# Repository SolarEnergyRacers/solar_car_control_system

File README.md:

`` SolarEnergyRacers

---

# Solar Car Control System

## ESP32 Pinout & Wiring

**_Wiring_**:

## Wiring / Port Usage

| Device:Port         | Functionality          |
| :------------------ | :--------------------- |
| **_ESP32_** | main micro processor   |
| ESP32:22            | I2C:SCL                |
| ESP32:23            | I2C:SDA                |
| ESP32:15            | SERIAL:TX              |
| ESP32:16            | SERIAL:RX              |
| ESP32:18            | SPI:MOSI               |
| ESP32:19            | SPI:MISO               |
| ESP32:5             | SPI:CLK                |
| ESP32:12            | 1Wire                  |
| ESP32:13            | GPIO:LED_BUILTIN       |
| ESP32:33            | GPIO:PCF8574_INTERRUPT |
| ESP32:14            | SPI:CS_SD_CARD         |
| ESP32:32            | SPI:CS_TFT_SCREEN      |
| ESP32:4             | SPI:DC                 |
| ESP32:21            | SPI:RST                |
| ESP32:25 DAC        | CAN:TX                 |
| ESP32:26 DAC        | CAN:RX                 |

| **_ADS1115_** |    Analog to digital converter    |
| :-------------------- | :--------------------------------: |
| ADC0, I2C Addr 0x48   |                                    |
| ADC0:0                | motor controller, speed indication |
| ADC0:1                |    Ibat: battery current sensor    |
| ADC0:2                |     Imot: motor current sensor     |
| ADC0:3                |       Ipv: pv current sensor       |
| ADC1, I2C Addr 0x49   |                                    |
| ADC1:0                |   Ubat: battery voltage (analog)   |
| ADC1:1                |   Umot: motorcontroller voltage   |
| ADC1:2                |                                    |
| ADC1:3                |                                    |
| ADC2, I2C Addr 0x4a   |                                    |
| ADC2:0                | steering wheel acceleration piezo |
| ADC2:1                | steering wheel deceleration piezo |
| ADC2:2                |                                    |
| ADC2:3                |                                    |

| **_MCP23014_** |      Input/Output extender      |
| :--------------------- | :-----------------------------: |
| **IOExt0**       |                                |
| IOExt0:0 in            | switch (status): battery on/off |
| IOExt0:1 in            |   switch (status): PV on/off   |
| IOExt0:2 in            |  switch (status): motor on/off  |
| IOExt0:3               |       ~~mc: eco/power~~       |
| IOExt0:4               |         ~~mc: on/off~~         |
| IOExt0:5 in            |    switch (status): fwd/rwd    |
| IOExt0:6               |         ~~pv: on/off~~         |
| IOExt0:7               |   output: battery fan on/off   |
|                        |                                |
| IOExt1:0               |     output: left indicator     |
| IOExt1:1               |     output: right indicator     |
| IOExt1:2               |          output: horn          |
| IOExt1:3               |       output: head light       |
| IOExt1:4               |          output: light          |
| IOExt1:5               |                                |
| IOExt1:6               |                                |
| IOExt1:7               |                                |
| **IOExt2**       |     steering wheel buttons     |
| IOExt2:0               |     button: left indicator     |
| IOExt2:1               |     button: right indicator     |
| IOExt2:2               |       button: head light       |
| IOExt2:3               |          button: light          |
| IOExt2:4               |          button: horn          |
| IOExt2:5               |          button: next          |
| IOExt2:6               |       button: power/speed       |
| IOExt2:7               |        button: set/reset        |

| **_ILI9341_** |             3.2" 320x240 display             |
| :-------------------- | :------------------------------------------: |
| ILI9341: CS           |         see ESP32:SPI:CS_TFT_SCREEN         |
| ILI9341: MOSI         |              see ESP32:SPI:MOSI              |
| ILI9341: MISO         | see ESP32:SPI:MISO (Pull Down: 10kΏ to GND) |
| ILI9341: CLK          |              see ESP32:SPI:CLK              |
| ILI9341: D/S          |           Pull Down: 10kΏ to GND           |
| ILI9341: SD_CS        |                                              |

| **_DS1803_** |       digital potentiometer       |
| :------------------- | :-------------------------------: |
| SCL:8                |         see ESP32:I2C:SCL         |
| SDA:9                |         see ESP32:I2C:SDA         |
| H0:12                |       VCC at 5V Powersupply       |
| W0:10                |       MC:acceleration input       |
| L0:11                | GND at 5V Powersupply + ESP32:GND |
| H1:1                 |       VCC at 5V Powersupply       |
| W1:3                 |      MC: deceleration input      |
| L1:2                 | GND at 5V Powersupply + ESP32:GND |
| A0:6                 |       GND for address 0x28       |
| A1:5                 |       GND for address 0x28       |
| A0:4                 |       GND for address 0x28       |

| **_DS1307_** | RTC, real time clock |
| :------------------- | :------------------: |
| SCL                  |  see ESP32:I2C:SCL  |
| SDA                  |  see ESP32:I2C:SDA  |

| **_Gyro+Acc_** | gyroscope & accelerator |
| :--------------------- | :---------------------: |
| SCL                    |    see ESP32:I2C:SCL    |
| SDA                    |    see ESP32:I2C:SDA    |

| **_Temp_** | temperature sensor |
| :----------------- | :----------------: |
| Temp0              |  see ESP32:1Wire  |
| Temp1              |  see ESP32:1Wire  |
| Temp2              |  see ESP32:1Wire  |
| Temp3              |  see ESP32:1Wire  |

| **_SD_** |         sd card         |
| :--------------- | :----------------------: |
| CS               | see ESP32:SPI:CS_SD_CARD |
| MOSI             |      see ESP32:MOSI      |
| MISO             |      see ESP32:MISO      |
| CLK              |      see ESP32:CLK      |
| D/S              |        required?        |

| **_Serial_** | serial telemetry communication |
| :------------------- | :----------------------------: |
| RX                   |      see ESP32:SERIAL:RX      |
| TX                   |      see ESP32:SERIAL:TX      |

| **_MPPT_** | maximum power point tracking communication |
| :----------------- | :----------------------------------------: |
| CAN Lo             |              see ESP32:CAN:Lo              |
| CAN Hi             |              see ESP32:CAN:Hi              |

| **_BMS_** | battery management system communication |
| :---------------- | :-------------------------------------: |
| CAN Lo            |            see ESP32:CAN:Lo            |
| CAN Hi            |            see ESP32:CAN:Hi            |

| **_ILI9341_** |             3.2" 320x240 display             |
| :-------------------- | :------------------------------------------: |
| CS                    |         see ESP32:SPI:CS_TFT_SCREEN         |
| MOSI                  |              see ESP32:SPI:MOSI              |
| MISO                  | see ESP32:SPI:MISO (Pull Down: 10kΏ to GND) |
| CLK                   |              see ESP32:SPI:CLK              |
| D/S                   |           Pull Down: 10kΏ to GND           |

| **_DS1803_** |       digital potentiometer       |
| :------------------- | :-------------------------------: |
| SCL:8                |         see ESP32:I2C:SCL         |
| SDA:9                |         see ESP32:I2C:SDA         |
| H0:12                |       VCC at 5V Powersupply       |
| W0:10                |       MC:acceleration input       |
| L0:11                | GND at 5V Powersupply + ESP32:GND |
| H1:1                 |       VCC at 5V Powersupply       |
| W1:3                 |      MC: deceleration input      |
| L1:2                 | GND at 5V Powersupply + ESP32:GND |
| A0:6                 |       GND for address 0x28       |
| A1:5                 |       GND for address 0x28       |
| A0:4                 |       GND for address 0x28       |

|  |  |
| :- | :-: |

| **_Gyro&Acc_** | gyroscope & accelerator |
| :--------------------- | :---------------------: |
| SCL                    |    see ESP32:I2C:SCL    |
| SDA                    |    see ESP32:I2C:SDA    |

| **_Temp_** | temperature sensor |
| :----------------- | :----------------: |
| Temp0              |  see ESP32:1Wire  |
| Temp1              |  see ESP32:1Wire  |
| Temp2              |  see ESP32:1Wire  |
| Temp3              |  see ESP32:1Wire  |

| **_SD_** |         sd card         |
| :--------------- | :----------------------: |
| CS               | see ESP32:SPI:CS_SD_CARD |
| MOSI             |      see ESP32:MOSI      |
| MISO             |      see ESP32:MISO      |
| CLK              |      see ESP32:CLK      |
| D/S              |        required?        |

| **_Serial_** | serial telemetry communication |
| :------------------- | :----------------------------: |
| RX                   |      see ESP32:SERIAL:RX      |
| TX                   |      see ESP32:SERIAL:TX      |

| **_MPPT_** | maximum power point tracking communication |
| :----------------- | :----------------------------------------: |
| CAN Lo             |              see ESP32:CAN:Lo              |
| CAN Hi             |              see ESP32:CAN:Hi              |

| **_BMS_** | battery management system communication |
| :---------------- | :-------------------------------------: |
| CAN Lo            |            see ESP32:CAN:Lo            |
| CAN Hi            |            see ESP32:CAN:Hi            |

### Default Addresses

#### I2C

Scanning I2C addresses:

| Address | Device                         | Location       |
| ------- | ------------------------------ | -------------- |
| 0x00    | ESP32 I2C master               | main noard     |
| 0x19    | 6-axis inertial sensor, gyro   | main board     |
| 0x20    | MCP23014, Extended digital IOs | main board     |
| 0x21    | MCP23014, Extended digital IOs | steering wheel |
| 0x28    | DS1803, digital analog coder   | main board     |
| 0x48    | ADS1115, analog digital coder  | main board     |
| 0x49    | ADS1115, analog digital coder  | main board     |
| 0x4a    | ADS1115, analog digital coder  | steering wheel |
| 0x68    | DS1307, real time clock        | main board     |
| 0x69    | 6-axis inertial sensor, gyro   | main board     |

### Further Documentation and Findings

- [DOCU--ILI934-MCP230176-ESP32-Hazzy](docs/DOCU--ILI934-MCP23017-ESP32-Hazzy.md)
- Docu [MCP23017](docs/MCP23017.md)

## PlatformIO - Command Guide

**_Build project_**: `platformio run`

**_Upload firmware_**: `platformio run --target upload`

**_Build specific environment_**: `platformio run -e esp32dev`

**_Upload firmware for the specific environment_**: `platformio run -e esp32dev --target upload`

**_Monitor device_**: `platformio run device monitor`

**_Clean build files_**: `platformio run --target clean`

## License

This project is published under the [GNU General Public License v3.0](LICENSE).

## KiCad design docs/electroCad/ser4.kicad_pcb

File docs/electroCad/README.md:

# ELT-Schema and Board Design

[toc]

## Open Questions

- [ ] Do we need 5V and 3.3V on Main board?
- [ ] Should we provide additional 5V to Steering-wheel board (brightness)?
- [ ] Do we need one or two CAN bus transceivers?
- [ ] The new designed elements (PCF, ADS) and other parts need to add a footprint in library

## Rules and Hints

- all new for SER4 designed elements should get the tag "SER4"

## Main-board

### Layout Idea

- Board 150x100

- --> The IO and ADC board are stripped of of all connectors and reassembled, see below) 

To change connectors:

- PCF8574 boards
  - remove all plugs
  - reassembly 9 pin plug (8 IOs and Interrupt) and 4 pin I2C pin (I2C) on backside
  - can possibly be shortened a little
  - drill mounting hole
- ADS1115 grove boards
  - remove all plugs and connectors
  - reassembly 4 pins (analog in) and 4 pins (I2C) on backside
- CAN
  - IC names missing in doc/data-sheets

## Steering-wheel Board

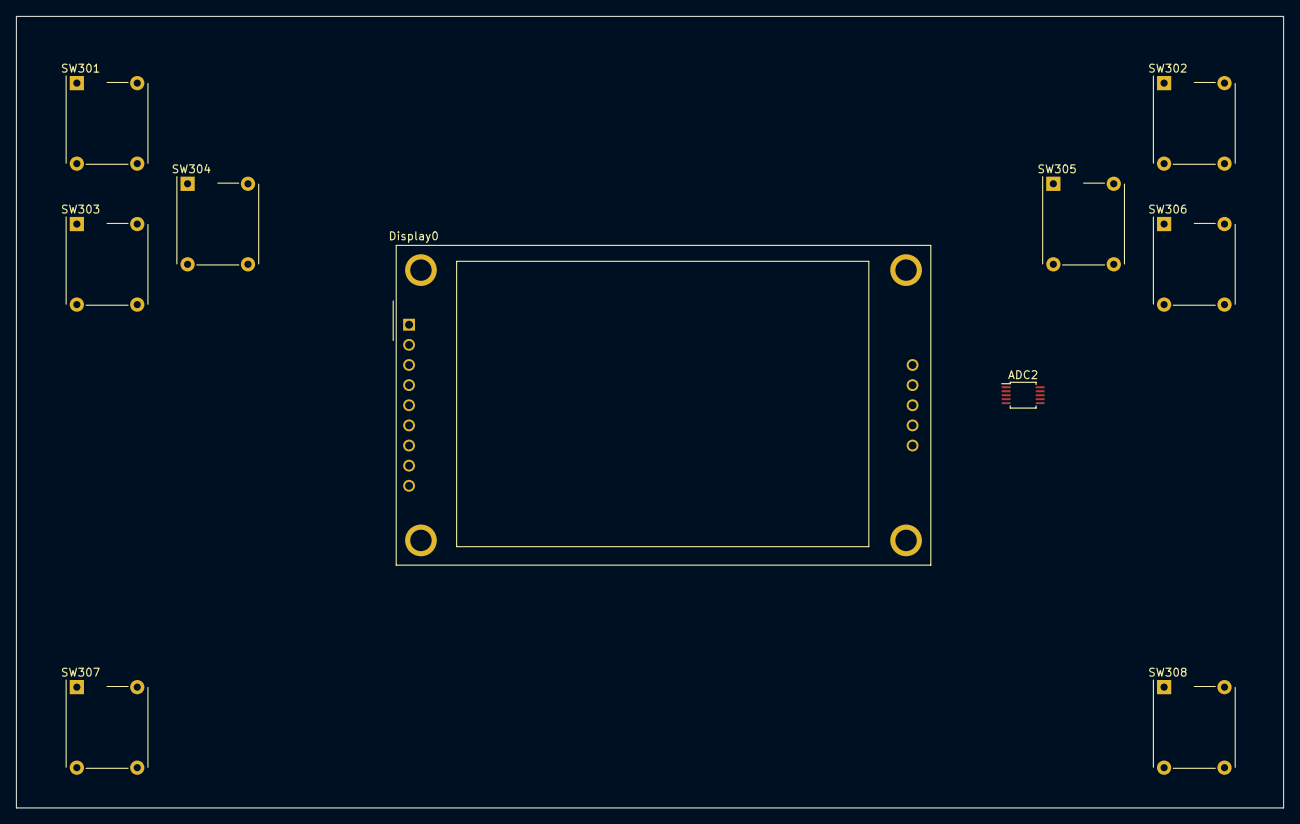
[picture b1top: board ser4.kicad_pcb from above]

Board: 2 copper layers, 159.8 x 99.8 mm, 10 parts (0 on the bottom side), 10 nets, no tracks yet.

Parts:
ADC2: ADS1115IDGS; TSSOP-10_3x3mm_P0.5mm
Display0: CR2013-MI2120
SW301, SW302, SW303, SW304, SW305, SW306, SW307, SW308: SW_MEC_5E; SW_MEC_5GTH9

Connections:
GND: ADC2.3, Display0.2
unnamed: SW301.1, SW301.2
unnamed: SW302.1, SW302.2
unnamed: SW303.1, SW303.2
unnamed: SW304.1, SW304.2
unnamed: SW305.1, SW305.2
unnamed: SW306.1, SW306.2
unnamed: SW307.1, SW307.2
unnamed: SW308.1, SW308.2
VCC: ADC2.8, Display0.1

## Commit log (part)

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2021-07-15 Apply prettier and clang-format
2021-07-15 fix: display of first numbers at position 2 to 4 fix: lifeSign blink
2021-07-26 backup
2021-07-27 clean up
2021-07-28 remove delay(), not necessary!
2021-07-28 Fix push format (#79)
    * Fix formatting application that misses trigger for new build pipeline #62
    * Trigger clang-format
    * Apply prettier and clang-format
    * Trigger clang-format
    * Apply prettier and clang-format
    * Add new fail/pass system for the formatting #79
2021-08-07 chore: include ELT DCAD initial
2021-08-07 chire: cleanup
2021-08-07 chore: split into multi sheets
2021-08-08 chore: add some info texts
2021-08-10 chore: add reame for ELT
2021-08-10 chore: improve readme
2021-08-22 chore:assembly info PCF8574
2021-08-22 chore: assembly info PCF8574
2021-08-23 chore: add sizes
2021-08-23 chore: add mech constr
2021-08-29 chore: datasheets and fixed schema
2021-09-01 Add SD Card and RTC datasheets
2021-09-01 Add missing Prohelion BMS datasheets (CAN specs, ..)
2021-09-04 fix include statements
2021-09-04 cleanup ifdef constants
2021-09-06 Fix CAN issue / finally add CAN support #40 #4
2021-09-07 Rework IOExt to support multiple devices #86
2021-09-12 basic car state implemented
2021-09-27 Update from 3 to 4 devices
2021-09-27 Print message not only upon error, but also report success.
2021-09-27 Add missing comma.
2021-09-27 Fix instance array size
2021-09-27 Add full project guard name
2021-09-27 Add initial implementation of car speed pid control.
2021-09-28 Fix variable name, fix integer arithmetic
2021-09-28 Integrate CarSpeed class to FreeRTOS structure
2021-09-28 Remove redeclaration, add abstract_class extension
2021-10-02 Add initial implementation of car speed pid control. (#107)
    * Add initial implementation of car speed pid control.
    * Fix variable name, fix integer arithmetic
    * Fix class function implementation: add missing CarSpeed::
    * Integrate CarSpeed class to FreeRTOS structure
    * Remove redeclaration, add abstract_class extension
2021-10-02 creal name for pics
2021-10-02 make assets folder visible
2021-10-03 integrated: CarSpeed, new multi IOExt
2021-10-04 initial IO handler
2021-10-10 Added CANPacket Class and RX Logic
    - Added new CAN Library
    - Added CANPacket Class
    - Added basic CAN receiving logic
2021-10-10 add IO print to Status print
2021-10-10 Add missing include
2021-10-16 rename DriverDisplayC to DriverDisplay
2021-10-16 rfactor: renaming Display names and constants
2021-10-17 Added Input Buffer for CAN
    - Added CANRxBuffer Class
    Doesn't compile because non relevant part of the CAN library uses instructions not that are not available.
    Maybe forking CAN library and removing said part?
2021-10-18 prepareings for engineer display
2021-10-18 Fix clang-format
2021-10-19 include engineering display, step 1, clean ups
2021-10-20 Engineer Display values screen
2021-10-23 Engineering Display step 5
2021-10-25 - autofromat - engineer screen and driver screen - rtc integration (add ESP32Time lib) - CarControl initial
2021-10-25 switch indicator, light off at startup
2021-10-26 sort inputs
2021-10-26 format.sh
2021-11-02 - order library in platform.ini alphabetically - feat: SD-Card ser4 boot conform, reduce outputs - feat: RTC ser4 boot conform - fix: delete wrong paste data - allow init SPI - fix: names fixed, form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
2021-11-02 - remove wrong include
2021-11-06 stabalized display :)
2021-11-08 clean up all the stuff, use new semaphoreTake that can throw exception, make tft static remove lot of dublicated code
2021-11-12 reduce display actions if no value changed
2021-11-14 reduce program overhaed by simple C style
2021-11-14 display and ioext
2021-11-16 first commit with new board and MCP23017
2021-11-23 working interrupt, working relais, working break pedal
2021-11-24 initial paddle adjustment
2021-11-26 Feature/simplify-carstate (#120)
    * add speed calc
    * - order library in platform.ini alphabetically
    - feat: SD-Card ser4 boot conform, reduce outputs
    - feat: RTC ser4 boot conform
    - fix: delete wrong paste data
    - allow init SPI
2021-12-05 remove all char buffers, remove lots of printf calls, refactor paddle_adjust
2021-12-05 Reading MPPT and BMS data, CAN library fork
    - Added the possibility to read single bits as bool from CAN packet
    - Added code in comments to read MPPT and BMS data
    - Created fork of CAN library and deleted unnecessary parts, added it to dependencies
2021-12-20 write SD Card and view Displays
2021-12-20 use format.sh
2021-12-21 demo log file
2021-12-21 Fix duplicate objects
2021-12-21 remove and then ignore build folder
2021-12-21 use cout
2021-12-23 Use exact library version
2021-12-23 Fix formatting and hope for the best during build.. (#130)
    * Fix formatting and hope for the best during build..
    * Use exact library version
    * Downgrade BusIO to compatible version
2021-12-24 Fix formatting
2021-12-27 Move motor efficiency curve to dedicated folder
2021-12-27 Ignore build directory
2021-12-27 Add minimal data explanation
2021-12-28 add links between docus
2021-12-28 rename to new IOExt MDC23017
2021-12-30 feat: break pedal switch acc to 0 and dec to max
2021-12-30 initial Checklist.md, remember current speed and power
2022-01-01 fix spelling, cleanup, set default sleep to 300ms, set i2c clock to 200MHz, prepare memory daump, add formatting getTimeStamp for uptime
2022-01-02 improve checklist
2022-01-04 CAN rebase (#131)
    * Added CANPacket Class and RX Logic
    - Added new CAN Library
    - Added CANPacket Class
    - Added basic CAN receiving logic
    * Added Input Buffer for CAN
    - Added CANRxBuffer Class
2022-01-06 Add separate acceleration and deceleration output setpoints #138
2022-01-09 Update Status Electric, Review Regulations (planning)
2022-01-12 Move constants into definitions.h
2022-01-12 run local formatter
2022-01-13 fix merge mistake, add extern deklaration for ESP32SJA1000Class CAN
2022-01-13 Fix library include & formatting
2022-01-14 Replace platform_package (arduino-esp32 framework) from my personal to the forked solarenergyracers fork
2022-01-14 Remove unused datasheets
2022-01-14 Keep pdf datasheets only
2022-01-14 Add template to add documentation
2022-01-14 Source env again before run
2022-01-14 Remove duplicates and rename datasheet consistently
2022-01-23 Added max age and filter for CAN Frames
    - Added functionality to update data from certain frames in a reduced interval
    - Added functionality to filter certain frames
    - Added corresponding definitions in definitions.h
2022-01-24 merge, set console speed to 9600 some minor fixes
2022-01-24 chapter 8.8 reviewed
2022-01-24 capter 2.21, 2.26, 2.27 wcs reviewed
2022-01-28 initial PID
2022-02-07 Add separate acceleration and deceleration output setpoints (#148)
    * Add separate acceleration and deceleration output setpoints #138
    * Fix formatting
    * fix merge mistake,
    add extern deklaration for ESP32SJA1000Class CAN
    * Fix library include & formatting
    * Fix formatting
2022-02-07 new sterring wheel controls (preview)
2022-02-07 Fix formatting to pass all ci pipelines. Test ci pipeline protected branch enforcement
2022-02-11 chore: update HW changes chor: doc for xbee integration
2022-02-11 prepare integration for xbee (HW)
2022-02-12 hide "locked" info on engineering screen
2022-02-12 add target speed/value display
2022-02-12 format all
2022-02-13 fix types for targetpower, targetfloat
2022-02-13 add docs and datasheets
2022-02-13 Fix formatting to pass all ci pipelines. Test ci pipeline protected branch enforcement (#155)
2022-02-14 Fix tables
2022-02-14 Feature/reference-solar-cell (#162)
    * new sterring wheel controls (preview)
    * clean up
    * clean up
    * lock dac motor setting to 0 until paddles adjusted
    * add sdCardDetect
    * chore: update HW changes
2022-02-15 Fix and move DisplayValue.h to a dedicated component
2022-02-15 CANBus-CarState interaction
    Added primary CAN Bus data to CarState
2022-02-22 prepareation steps for HC-12
2022-02-22 initial: serial radio communication
2022-02-23 Fix mistake in function defintion
2022-02-27 querry overload
2022-02-28 first try Console usage with Serial, Serial2, HC-12
2022-03-06 Cleanup
2022-03-06 Reformat
2022-03-10 Minor fix & format
2022-03-18 new pin layout steeringwheel, handling with +- const. value
2022-03-23 first part of adoptions after review
2022-03-23 fix after review
2022-03-23 buffered serial2 transfer (commented out)
2022-03-24 Remove this-> in CANBus.cpp
2022-03-27 Remove this-> and reformat
2022-03-28 Refactor car speed
2022-03-28 Adjust the two DAC ports to match the physical functionality (PORT0: acceleration & external IO for fwd/rev, PORT1: recuperation)
2022-03-29 Replace manually set version numbers with current branch and commit hash.
2022-03-29 Move debug enable flag from a macro to a run-time variable.
2022-03-29 Set static version
2022-03-29 Add header
2022-03-29 Remove unnecessary includes
2022-03-29 Standardize std usage
2022-03-30 Refactor debug to runtime (#177)
    * Refactor car speed
    * Add stack size as a create_task parameter
    * Move debug enable flag from a macro to a run-time variable.
2022-03-30 allow gyro anbd fix gyro locks
2022-03-30 Resolve all mentioned issues in the thread
2022-03-30 Code refactoring (#179)
    * Set static version
    * Dead code removal
    * Add header
    * Remove unnecessary includes
    * Fix formatting artifacts
    * Standardize std usage
2022-03-30 fix: formatting
2022-03-30 Feature/serial radio console (#180)
    * initial docu with working demo code
    * prepareation steps for HC-12
    * initial: serial radio communication
    * querry overload
    * first try Console usage with Serial, Serial2, HC-12
    * intermideate state: both displays running
2022-03-31 feat: warning for about wrong PID value feat: initial ini file reader
2022-04-11 iLumen 2022 regulations
2022-04-11 add review chaptor for iEsc
2022-04-14 removed Chameleon class
2022-04-14 simplify limit control
2022-04-14 use CarDataLogPeriod and I2CFrequency
2022-04-18 intermediate backup
2022-04-23 read from sd card ini file
2022-05-14 format fixed
2022-05-16 remove calculation. give directly in cycles
2022-05-27 initial for main board V4
2022-05-27 formatted
2022-05-27 add fmtlib/fmt@ 8.1.1
2022-06-08 extract sleep_polling_ms from abstact into classes
2022-06-09 feat: main-v4 runs stable with base functions
2022-06-10 improve comdHandler with outputs to console
2022-06-14 improve/update help screnn
2022-06-15 fwd/bwd change
2022-07-01 chore: fix format
2022-07-03 add G (GreenLeight) and F (Fan) commands
2022-07-07 fomat all
2022-07-08 fix: sd card recognized at start
2022-07-08 fix: clean strings for log
2022-07-08 feat: command for setting RTC date time
2022-07-17 fix: optimized verbose modes, feat: add verbose mode for DAC
2022-07-26 chore: unify data in manuals
2022-07-26 chore: exclude console logs
2022-07-26 feat: imporve console log for ADC and DAC
2022-07-26 speed
2022-07-26 fix: all speeds in km/h feat: add 'k' to view PID parameters
2022-07-29 fix: improve output of cmd handling on console
2022-07-30 feat: buttons control mode (w/o paddles)
2022-07-31 fix: cleanup not useful i2cfrequency variable
2022-08-01 fix: improve normalize of paddle values
2022-08-03 updates for board v5
2022-08-21 fix: cleanup not useful i2cfrequency variable fix: add 'd:' for telemetry records
2022-08-25 CAN bus live test with MPPT working
2022-08-25 add verboseMode for CANbus
2022-08-28 remove unnecessary name
2022-08-28 remove paddle adjust message if ok after a second
2022-09-08 green light working
2022-09-08 cleanup test output
2022-09-14 cleaup code
2022-09-16 feat: downsize break pedal recuperation, prepare new getDateTime()
2022-09-16 fix: esp32time integration, simple time format
2022-09-17 fix: add missing ',' in csv

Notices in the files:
README.md:
License: GPL v3
